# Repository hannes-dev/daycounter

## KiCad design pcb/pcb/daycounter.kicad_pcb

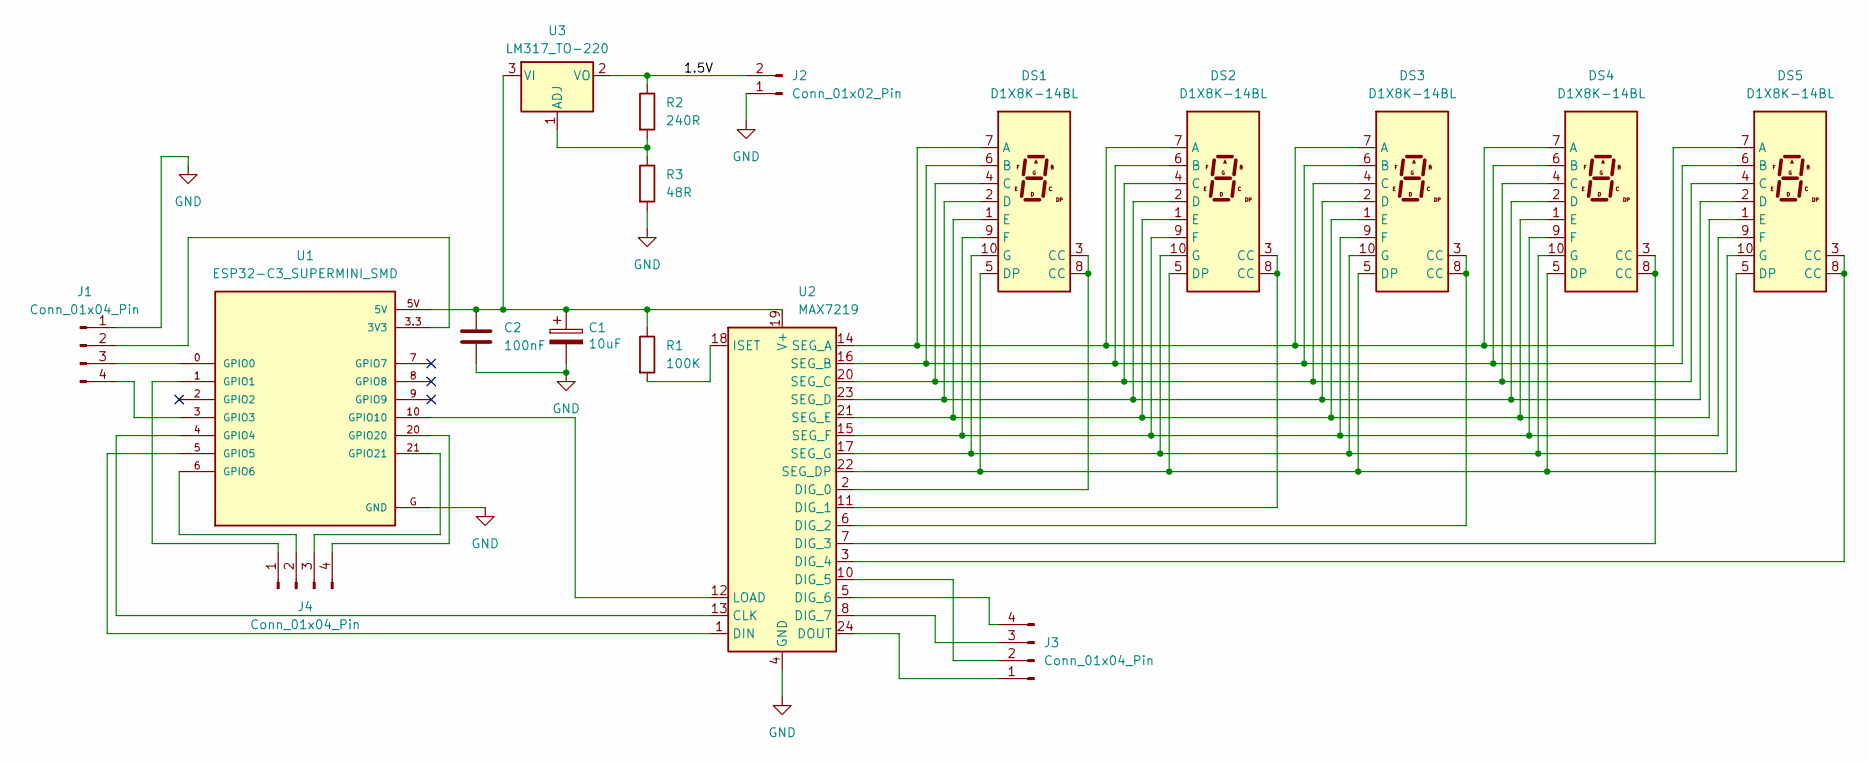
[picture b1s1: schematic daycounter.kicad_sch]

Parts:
C1: 10uF; CP_Radial_D5.0mm_P2.50mm
C2: 100nF; C_Disc_D3.0mm_W1.6mm_P2.50mm
DS1, DS2, DS3, DS4, DS5: D1X8K-14BL; 1106AW_1inch_7_segment
J1, J3, J4: Conn_01x04_Pin; PinHeader_1x04_P2.54mm_Vertical
J2: Conn_01x02_Pin; PinHeader_1x02_P2.54mm_Vertical
R1: 100K; R_Axial_DIN0207_L6.3mm_D2.5mm_P10.16mm_Horizontal
R2: 240R; R_Axial_DIN0207_L6.3mm_D2.5mm_P10.16mm_Horizontal
R3: 48R; R_Axial_DIN0207_L6.3mm_D2.5mm_P10.16mm_Horizontal
U1: ESP32-C3_SUPERMINI_SMD; MODULE_ESP32-C3_SUPERMINI
U2: MAX7219; DIP-24_W7.62mm
U3: LM317_TO-220; TO-220-3_Vertical

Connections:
/1.5V: J2.2, R2.1, U3.2 (VO)
GND: C1.2, C2.2, J1.1, J2.1, R3.2, U1.G (GND), U2.4 (GND), U2.9 (GND)
unnamed: DS1.7 (A), DS2.7 (A), DS3.7 (A), DS4.7 (A), DS5.7 (A), U2.14 (SEG_A)
unnamed: DS1.6 (B), DS2.6 (B), DS3.6 (B), DS4.6 (B), DS5.6 (B), U2.16 (SEG_B)
unnamed: DS1.4 (C), DS2.4 (C), DS3.4 (C), DS4.4 (C), DS5.4 (C), U2.20 (SEG_C)
unnamed: DS1.2 (D), DS2.2 (D), DS3.2 (D), DS4.2 (D), DS5.2 (D), U2.23 (SEG_D)
unnamed: DS1.5 (DP), DS2.5 (DP), DS3.5 (DP), DS4.5 (DP), DS5.5 (DP), U2.22 (SEG_DP)
unnamed: DS1.1 (E), DS2.1 (E), DS3.1 (E), DS4.1 (E), DS5.1 (E), U2.21 (SEG_E)
unnamed: DS1.9 (F), DS2.9 (F), DS3.9 (F), DS4.9 (F), DS5.9 (F), U2.15 (SEG_F)
unnamed: DS1.10 (G), DS2.10 (G), DS3.10 (G), DS4.10 (G), DS5.10 (G), U2.17 (SEG_G)
unnamed: J1.2, U1.3.3 (3V3)
unnamed: J1.3, U1.0 (GPIO0)
unnamed: J1.4, U1.3 (GPIO3)
unnamed: J3.1, U2.24 (DOUT)
unnamed: J3.2, U2.10 (DIG_5)
unnamed: J3.3, U2.8 (DIG_7)
unnamed: J3.4, U2.5 (DIG_6)
unnamed: J4.1, U1.1 (GPIO1)
unnamed: J4.2, U1.6 (GPIO6)
unnamed: J4.3, U1.21 (GPIO21)
unnamed: J4.4, U1.20 (GPIO20)
unnamed: U1.4 (GPIO4), U2.13 (CLK)
unnamed: U1.5 (GPIO5), U2.1 (DIN)
unnamed: U1.10 (GPIO10), U2.12 (LOAD)
unnamed: DS1.3 (CC), DS1.8 (CC), U2.2 (DIG_0)
unnamed: DS2.3 (CC), DS2.8 (CC), U2.11 (DIG_1)
unnamed: DS3.3 (CC), DS3.8 (CC), U2.6 (DIG_2)
unnamed: DS4.3 (CC), DS4.8 (CC), U2.7 (DIG_3)
unnamed: DS5.3 (CC), DS5.8 (CC), U2.3 (DIG_4)
unnamed: R1.2, U2.18 (ISET)
unnamed: C1.1, C2.1, R1.1, U1.5V, U2.19 (V+), U3.3 (VI)
unnamed: R2.2, R3.1, U3.1 (ADJ)

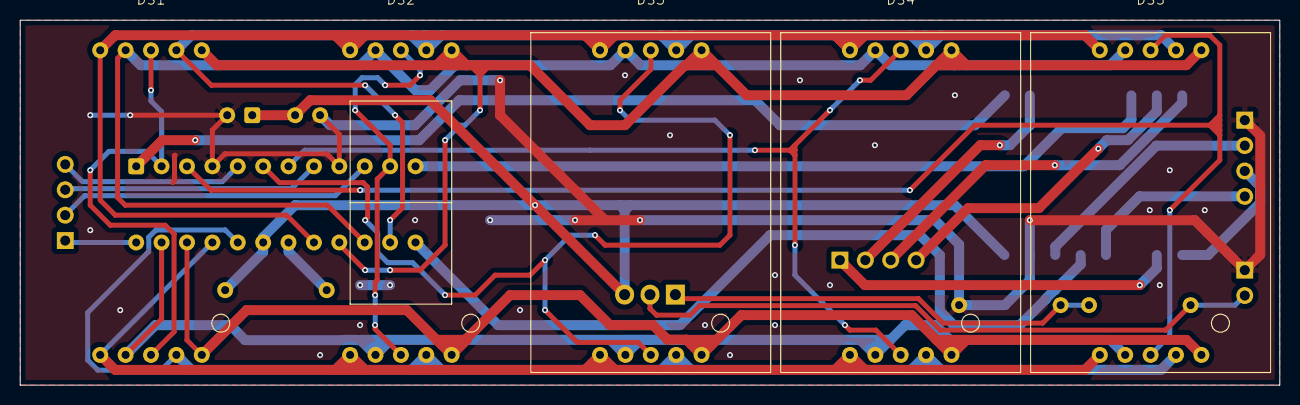
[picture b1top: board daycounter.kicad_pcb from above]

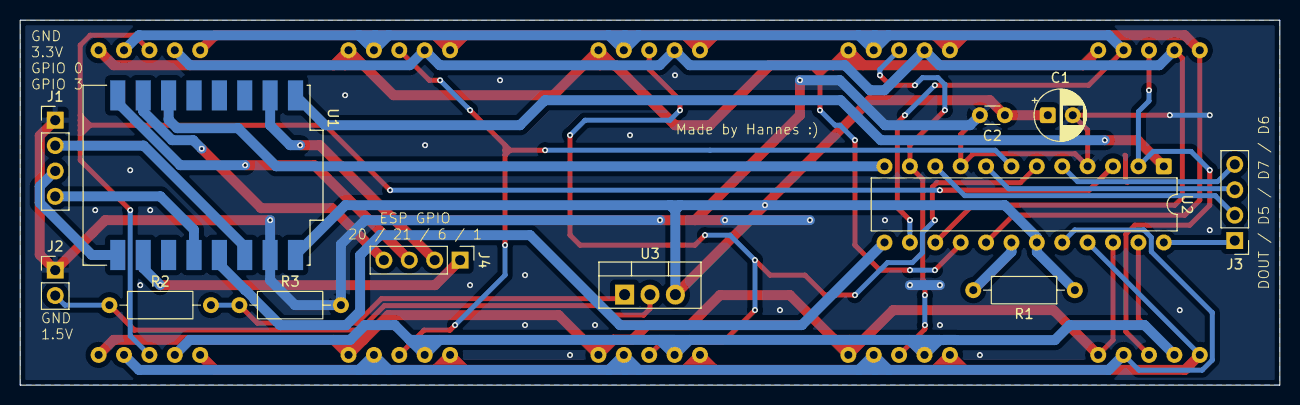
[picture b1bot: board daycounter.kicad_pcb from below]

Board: 2 copper layers, 126.0 x 36.5 mm, 17 parts (12 on the bottom side), 32 nets.

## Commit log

2025-09-28 basic traces
2025-09-28 1.5v traces
2025-09-28 pcb done
2025-09-28 full plane
2025-10-31 finished board
2025-10-31 rename and move pcb
2025-10-31 add basic rotating code
2025-10-31 reorder files
2025-10-31 cleanup code
